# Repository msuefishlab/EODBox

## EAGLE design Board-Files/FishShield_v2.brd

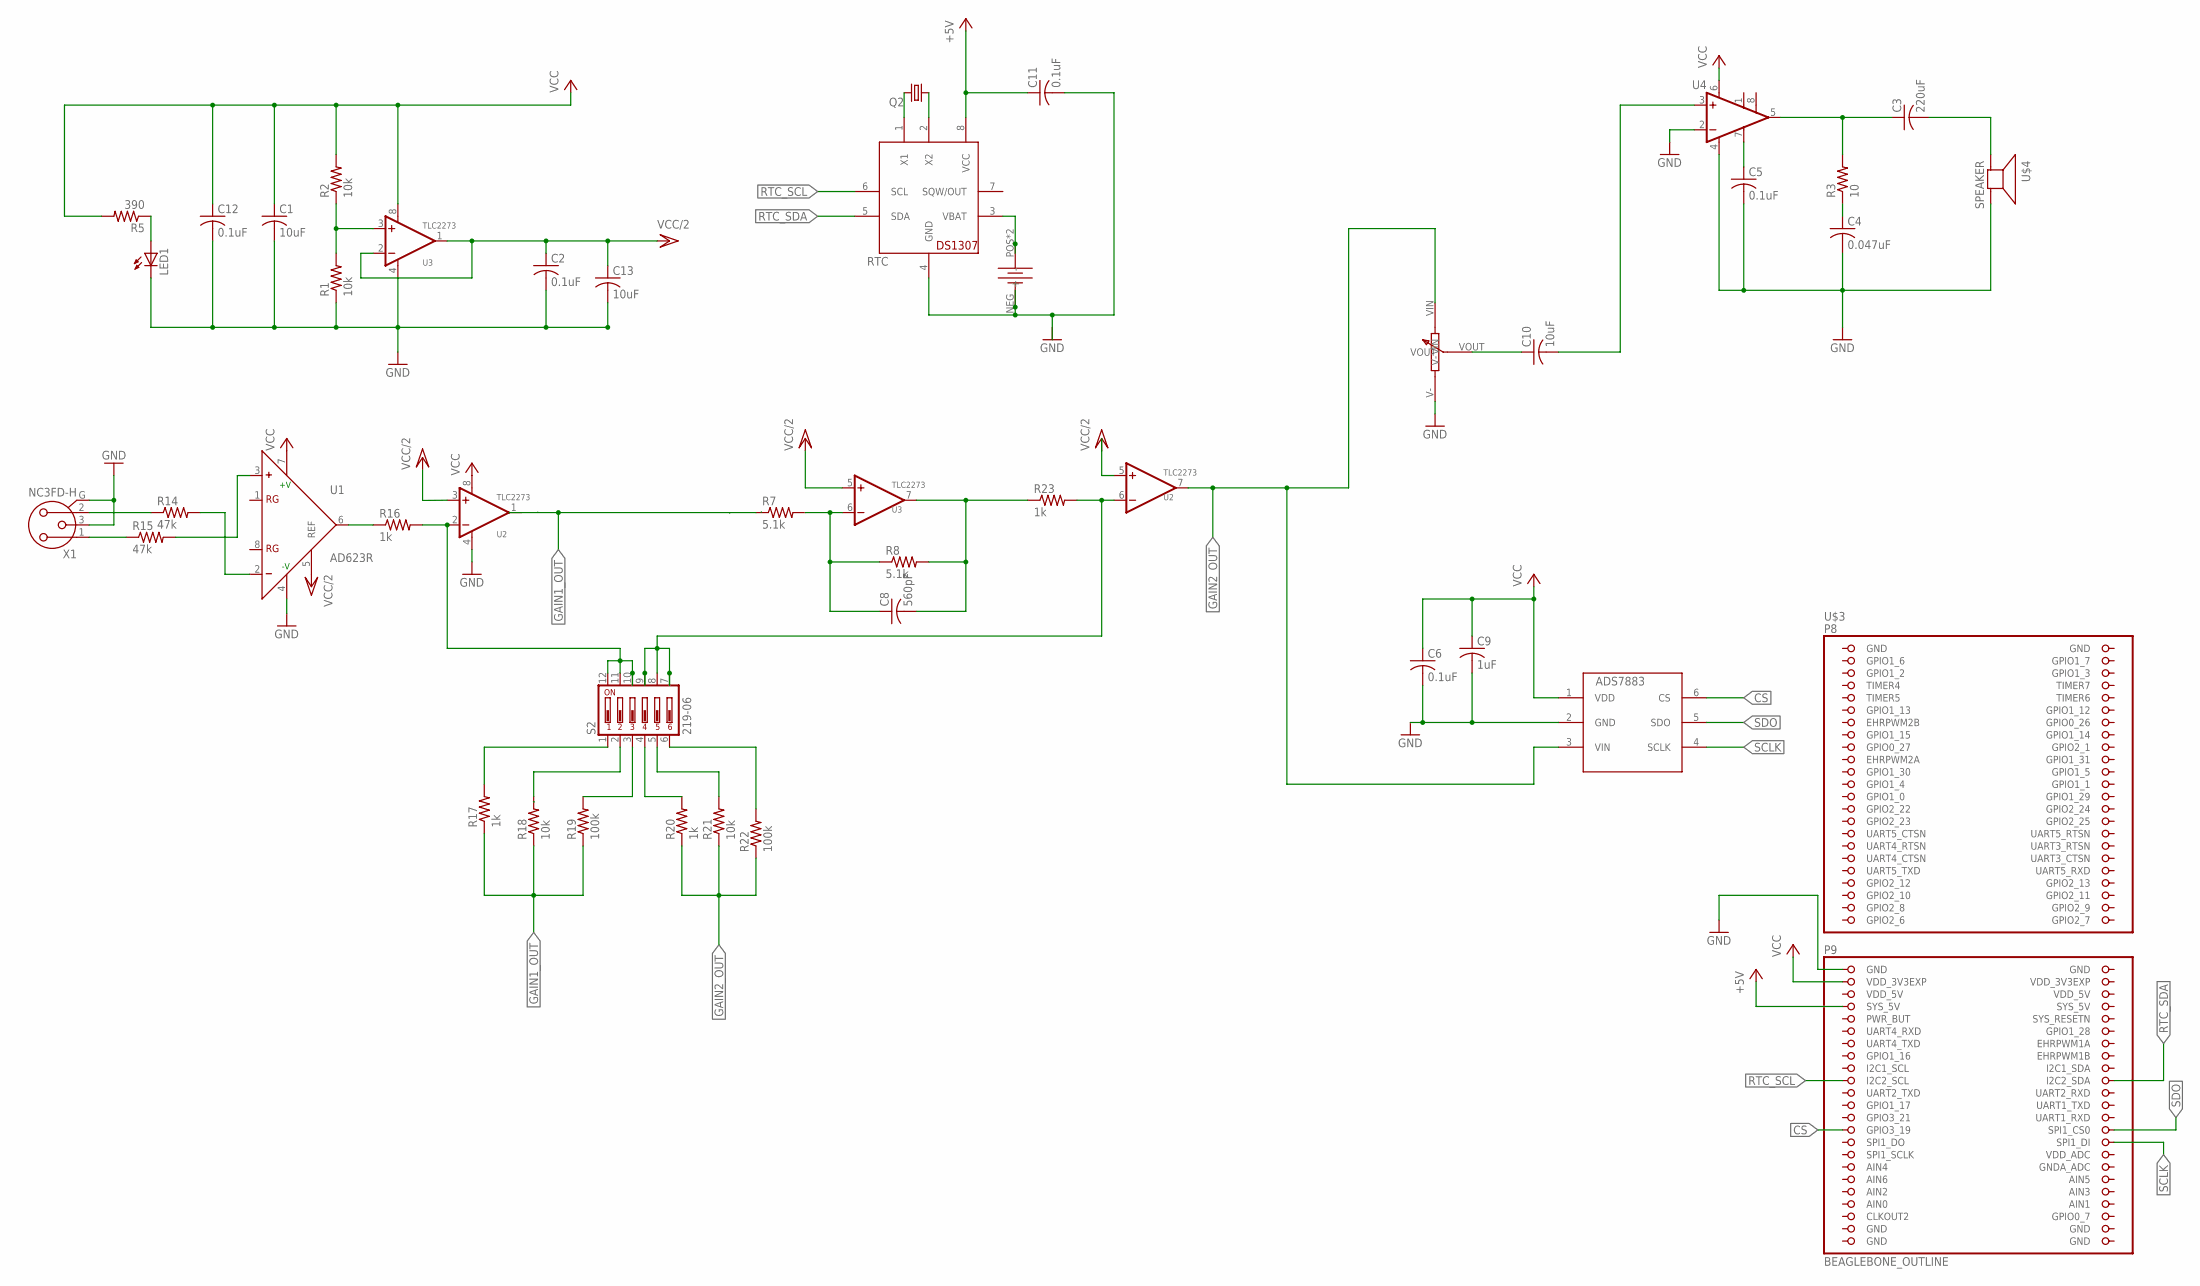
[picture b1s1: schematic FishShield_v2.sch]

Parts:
ADC: ADS7883; SOT23-6
C1, C13: 10uF; C050-024X044
C2, C5, C6, C11, C12: 0.1uF; C050-024X044
C3: 220uF; C050-050X075
C4: 0.047uF; C050-024X044
C8: 560pF; C050-024X044
C9: 1uF; C050-024X044
C10: 10uF; C050-030X075
LED1: LEDLSU260; LSU260
P1: POT; 10K_POT
Q2: CRYSTALTC38H; TC38H
R1, R2, R18, R21: 10k; 0204V
R3: 10; 0204V
R5: 390; 0204V
R7, R8: 5.1k; 0204V
R14, R15: 47k; 0204V
R16, R17, R20, R23: 1k; 0204V
R19, R22: 100k; 0204V
RTC: DS1307; DIL08
S2: 219-06; CTS-219-06
U1: AD623R; SO8
U2: U2; SOIC-8
U3: U3; SOIC-8
U4: LM386M-1; SO08
U$3: BEAGLEBONE_OUTLINE; BEAGLEBONE_SHIELD
U$4: SPEAKER
U$5: BATTERY
X1: NC3FD-H

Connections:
+5V: C11.1, RTC.8 (VCC), U$3.53 (SYS_5V)
AIN0: U$3.85 (AIN0)
CS: ADC.6 (CS), U$3.73 (GPIO3_19)
GAIN1: R16.2, S2.10, S2.11, S2.12, U2.2 (-IN)
GAIN1_OUT: R7.1, R17.1, R18.1, R19.1
GAIN2: R23.2, S2.7, S2.8, S2.9, U2.6 (-IN)
GAIN2_OUT: ADC.3 (VIN), P1.VIN, R20.1, R21.1, R22.1, U2.7 (OUT)
GND: ADC.2 (GND), C1.2, C2.2, C4.2, C5.2, C6.2, C9.2, C12.2, C13.2, LED1.K (C), P1.V-, R1.1, U1.4 (-V), U2.4 (V-), U3.4 (V-), U4.2 (-IN), U4.4 (GND), U$3.1 (GND), U$3.2 (GND), U$3.47 (GND), U$3.48 (GND), U$3.89 (GND), U$3.90 (GND), U$3.91 (GND), U$3.92 (GND), U$4.P$1 (-), X1.3, X1.G
unnamed: R14.1, X1.2
unnamed: R15.2, U1.3 (+)
unnamed: R14.2, U1.2 (-)
unnamed: R16.1, U1.6 (OUT)
unnamed: R1.2, R2.1, U3.3 (+IN)
unnamed: LED1.A, R5.1
unnamed: RTC.3 (VBAT), U$5.POS (+), U$5.POS2 (+)
unnamed: C10.1, P1.VOUT
unnamed: C8.1, R7.2, R8.1, U3.6 (-IN)
unnamed: C8.2, R8.2, R23.1, U3.7 (OUT)
unnamed: R20.2, S2.4
unnamed: C10.2, U4.3 (+IN)
unnamed: C5.1, U4.7 (BYPASS)
unnamed: C3.1, R3.2, U4.5 (OUT)
unnamed: R17.2, S2.1
unnamed: C3.2, U$4.P$2 (+)
unnamed: R21.2, S2.5
unnamed: R22.2, S2.6
unnamed: R18.2, S2.2
unnamed: R19.2, S2.3
unnamed: Q2.1, RTC.2 (X2)
unnamed: C4.1, R3.1
unnamed: Q2.2, RTC.1 (X1)
unnamed: C11.2, RTC.4 (GND), U$5.NEG (-)
R15: R15.1, X1.1
RTC_SCL: RTC.6 (SCL), U$3.65 (I2C2_SCL)
RTC_SDA: RTC.5 (SDA), U$3.66 (I2C2_SDA)
SCLK: ADC.4 (SCLK), U$3.76 (SPI1_DI)
SDO: ADC.5 (SDO), U$3.74 (SPI1_CS0)
VCC: ADC.1 (VDD), C1.1, C6.1, C9.1, C12.1, R2.2, R5.2, U1.7 (+V), U2.8 (V+), U3.8 (V+), U4.6 (VS), U$3.49 (VDD_3V3EXP)
VCC/2: C2.1, C13.1, U1.5 (REF), U2.3 (+IN), U3.1 (OUT), U3.2 (-IN), U3.5 (+IN)
VDD_3V3EXP: U$3.50 (VDD_3V3EXP)
VDD_5V: U$3.51 (VDD_5V), U$3.52 (VDD_5V)

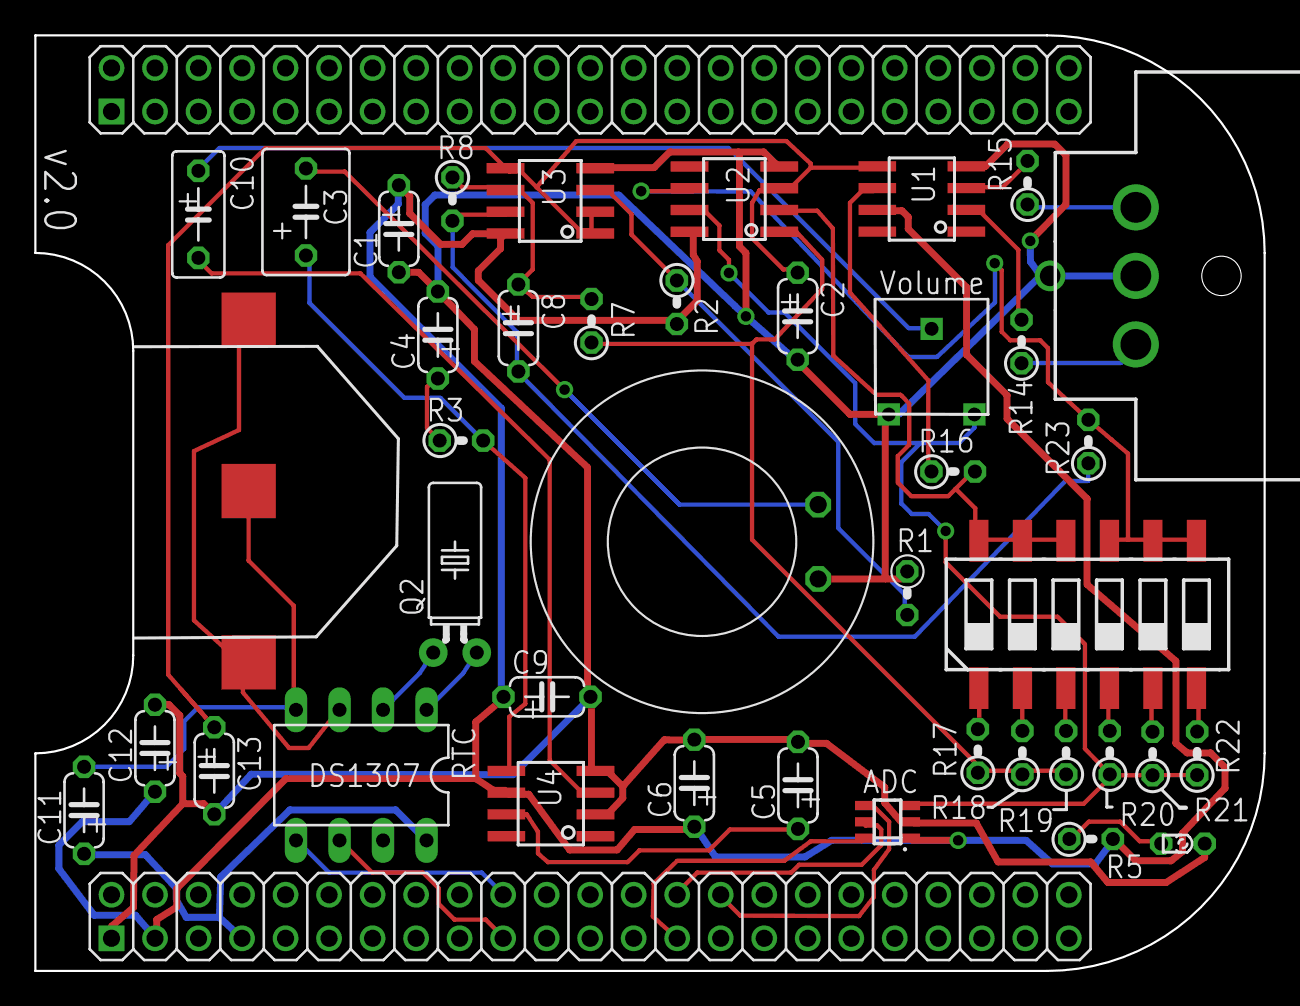
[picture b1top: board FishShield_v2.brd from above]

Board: 2 copper layers, 71.8 x 54.6 mm, 42 parts (0 on the bottom side), 39 nets.

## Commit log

2016-05-20 Initial upload of EOD recording code
2016-05-20 Rename Fishy_v1.c to Programs/Fishy_v1.c
2016-05-22 Initial upload of Translate.cpp
2016-05-22 Initial upload of PRU code
2016-05-22 Initial upload of PRU clock code
2016-05-22 Initial upload of the gnuplot script
2016-05-22 Initial upload of SD Card formatting script
2016-05-22 Rename SDCard_format.sh to Scripts/SDCard_format.sh
2016-05-22 Initial upload of the PRU memory formatting script
2016-05-22 Initial upload of text for the service file
2016-05-22 Initial upload of the make file
2016-05-22 Initial upload of device tree blob
2016-05-22 Initial upload of device tree overlay
2016-05-22 Rename EBB-PRU-ADC.dts to Device-Tree-overlays/EBB-PRU-ADC.dts
2016-05-22 Initial upload of board file
2016-05-22 Rename FishShield_v2.brd to Board-Files/FishShield_v2.brd
2016-05-22 Initial upload of schematic
2016-05-26 Created Documentation
2016-05-26 added beaglebone modification instructions
2016-05-26 edits
2016-05-26 Uploaded Documentation on External Storage
2016-05-26 uploaded PRU Modification Instructions
2016-05-26 Uploaded RTC Document
2016-05-26 Uploaded Background on Device & Edits
2016-05-26 Added CC License

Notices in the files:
parts and their libraries:
SparkFun-Aesthetics: Licensing: Creative Commons ShareAlike 4.0 International - https://creativecommons.org/licenses/by-sa/4.0
